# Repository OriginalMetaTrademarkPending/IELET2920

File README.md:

# IELET2920
Bachelor thesis on the research and development of next-generation handgrip trainers.

# Description of the task
In essence, the task is composed of the following parts:
- Mathematical modelling of the system. Due to the nature of this thesis, the model cannot be parameterized through a theoretical approach.
- Estimation of the parameters of the model. Referring to the point above, a least squares estimator has been used to estimate the model parameters.
- Kalman filter design. This is the final point of the design, which aims at improving the measurements, as well as estimating the hidden variable (fatigued muscle mass).

Here it is important to note that the task includes a significant amount of hardware design, especially in the domain of 3D-modelling, 3D-printing and PCB design.

# Parameter estimation

Until now, 5 tests have been completed. The results are shown below:

## Test 1: data.csv

$\theta_{af} = 0.0258$
$\theta_{ar} = 12.9653$
$\theta_{ra} = 1.8997$
$\theta_{fa} = 0.0230$
$M = 7.5095$
Sum of squares: 238.7625

## Test 2: test1.csv

$\theta_{af} = 0.0427$
$\theta_{ar} = 341.1526$
$\theta_{ra} = 3.1696$
$\theta_{fa} = 0.0747$
$M = 6.3241$
Sum of squares: 305.6513

## Test 3: test2.csv

$\theta_{af} = 0.0216$
$\theta_{ar} = 29.7083$
$\theta_{ra} = 4.9487$
$\theta_{fa} = 0$
$M = 7.4149$
Sum of squares: 297.8530

## Test 4: test3.csv

$\theta_{af} = 1.2019$
$\theta_{ar} = 75.4510$
$\theta_{ra} = 2.3210$
$\theta_{fa} = 1.0925$
$M = 12.1936$
Sum of squares: 954.0013

## Test 5: test4.csv

$\theta_{af} = 0.1093$
$\theta_{ar} = 517.0190$
$\theta_{ra} = 5.3904$
$\theta_{fa} = 0.1584$
$M = 5.9675$
Sum of squares: 767.8368

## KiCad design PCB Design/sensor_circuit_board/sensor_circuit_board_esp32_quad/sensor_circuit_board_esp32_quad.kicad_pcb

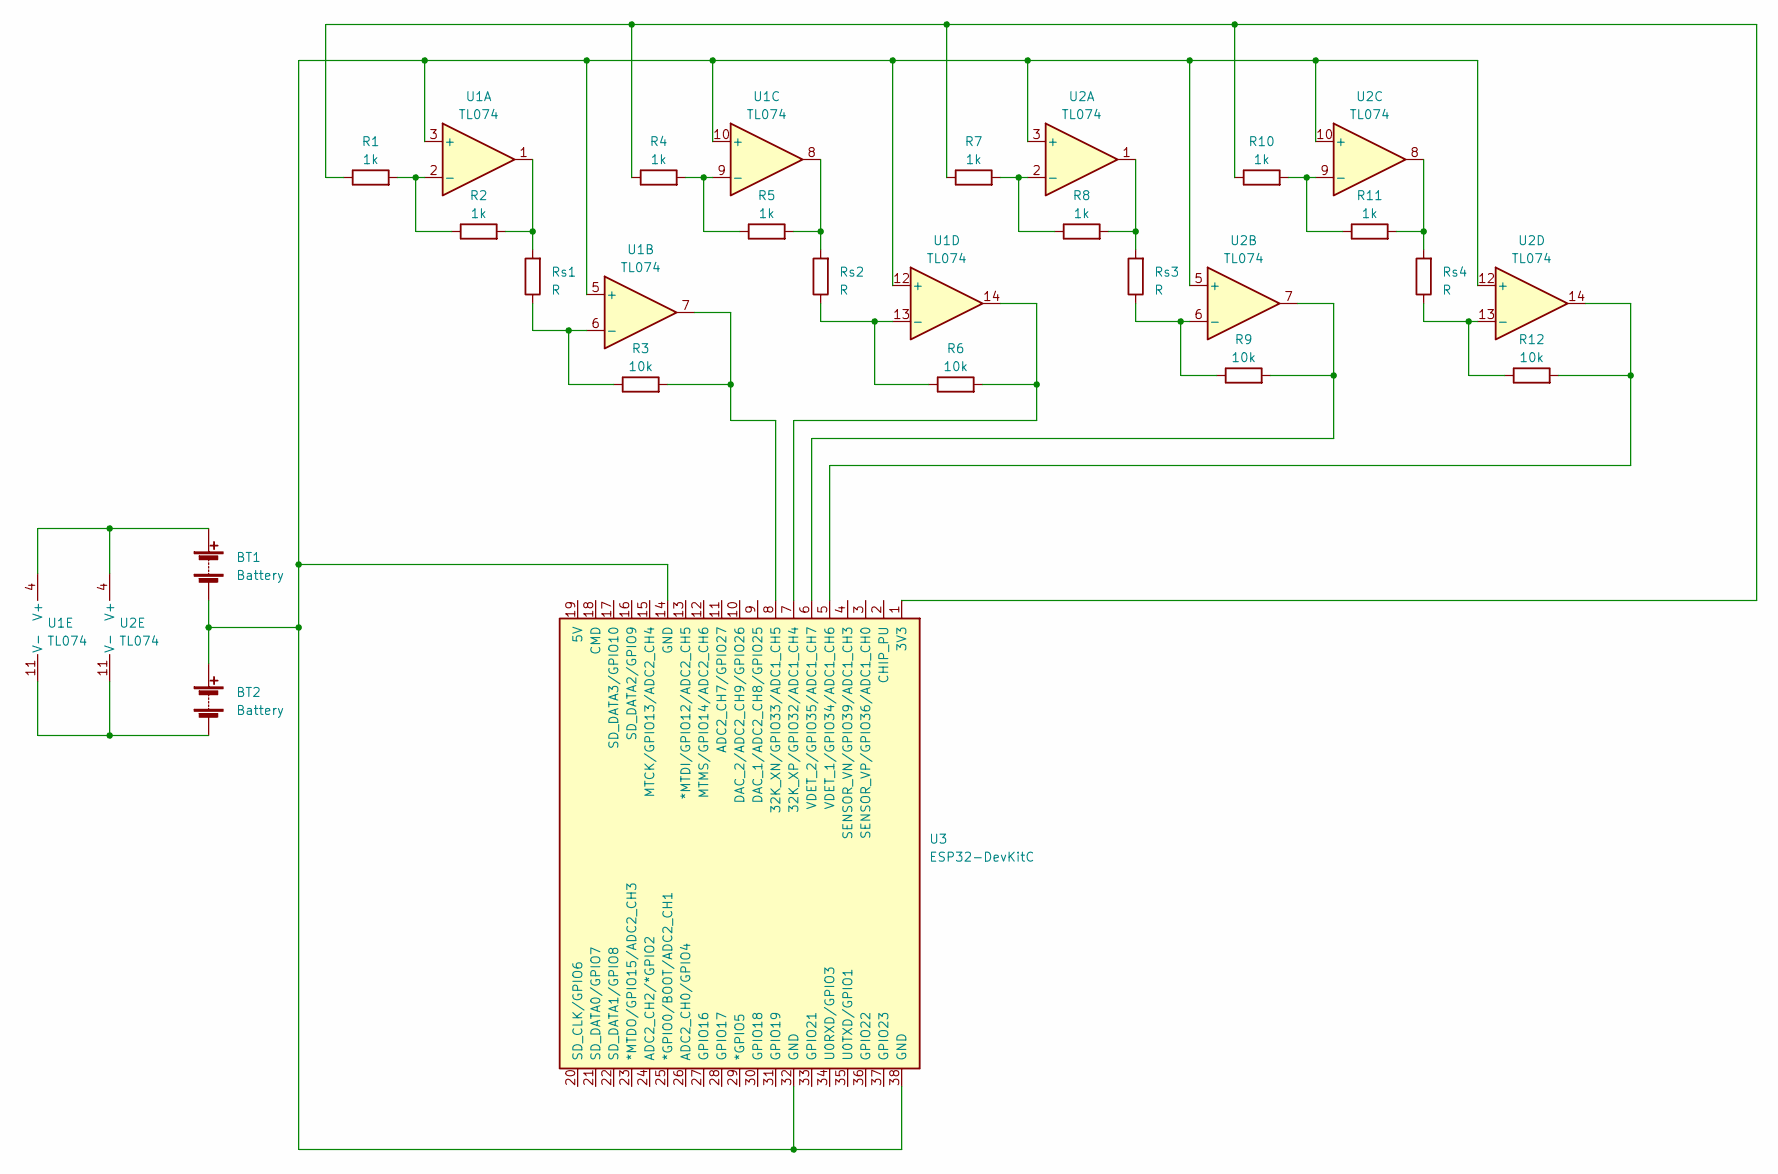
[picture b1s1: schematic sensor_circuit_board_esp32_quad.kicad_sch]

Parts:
BT1, BT2: Battery; BatteryHolder_Eagle_12BH611-GR
R1, R2, R4, R5, R7, R8, R10, R11: 1k; R_Axial_DIN0207_L6.3mm_D2.5mm_P7.62mm_Horizontal
R3, R6, R9, R12: 10k; R_Axial_DIN0207_L6.3mm_D2.5mm_P7.62mm_Horizontal
Rs1, Rs2, Rs3, Rs4: R; D_DO-15_P2.54mm_Vertical_AnodeUp
U1, U2: TL074; DIP-14_W7.62mm_LongPads
U3: ESP32-DevKitC

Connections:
unnamed: BT1.1 (+), U1.4 (V+), U2.4 (V+)
unnamed: BT1.2 (-), BT2.1 (+), U1.3 (+), U1.5 (+), U1.10 (+), U1.12 (+), U2.3 (+), U2.5 (+), U2.10 (+), U2.12 (+), U3.14 (GND), U3.32 (GND), U3.38 (GND)
unnamed: BT2.2 (-), U1.11 (V-), U2.11 (V-)
unnamed: R2.2, Rs1.2, U1.1
unnamed: R5.2, Rs2.2, U1.8
unnamed: R8.2, Rs3.2, U2.1
unnamed: R11.2, Rs4.2, U2.8
unnamed: R1.2, R2.1, U1.2 (-)
unnamed: R3.1, Rs1.1, U1.6 (-)
unnamed: R4.2, R5.1, U1.9 (-)
unnamed: R6.1, Rs2.1, U1.13 (-)
unnamed: R7.2, R8.1, U2.2 (-)
unnamed: R9.1, Rs3.1, U2.6 (-)
unnamed: R10.2, R11.1, U2.9 (-)
unnamed: R12.1, Rs4.1, U2.13 (-)
unnamed: R1.1, R4.1, R7.1, R10.1, U3.1 (3V3)
unnamed: R3.2, U1.7, U3.8 (32K_XN/GPIO33/ADC1_CH5)
unnamed: R6.2, U1.14, U3.7 (32K_XP/GPIO32/ADC1_CH4)
unnamed: R12.2, U2.14, U3.5 (VDET_1/GPIO34/ADC1_CH6)
unnamed: R9.2, U2.7, U3.6 (VDET_2/GPIO35/ADC1_CH7)

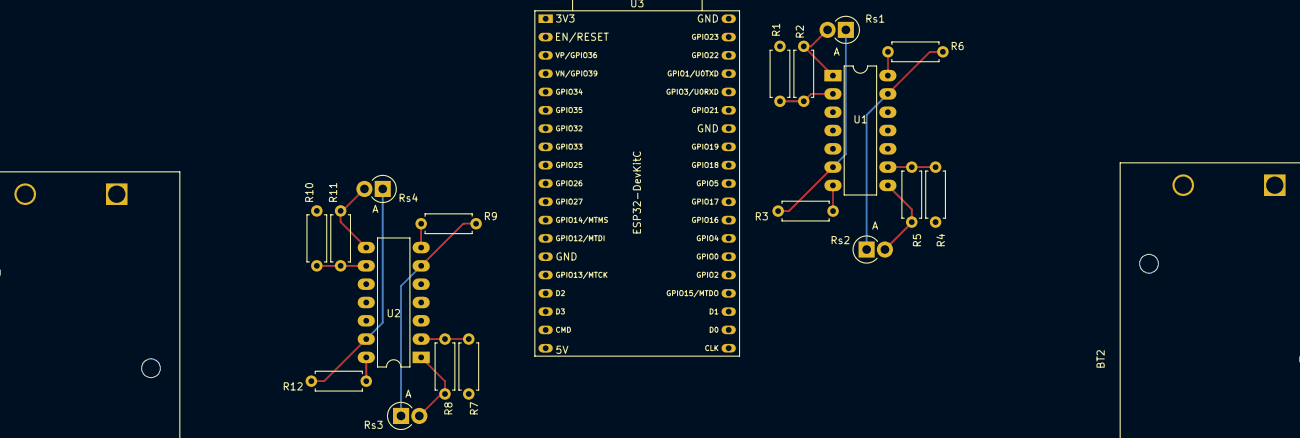
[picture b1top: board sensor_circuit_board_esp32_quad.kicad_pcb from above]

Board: 2 copper layers, 21 parts (0 on the bottom side), 20 nets.

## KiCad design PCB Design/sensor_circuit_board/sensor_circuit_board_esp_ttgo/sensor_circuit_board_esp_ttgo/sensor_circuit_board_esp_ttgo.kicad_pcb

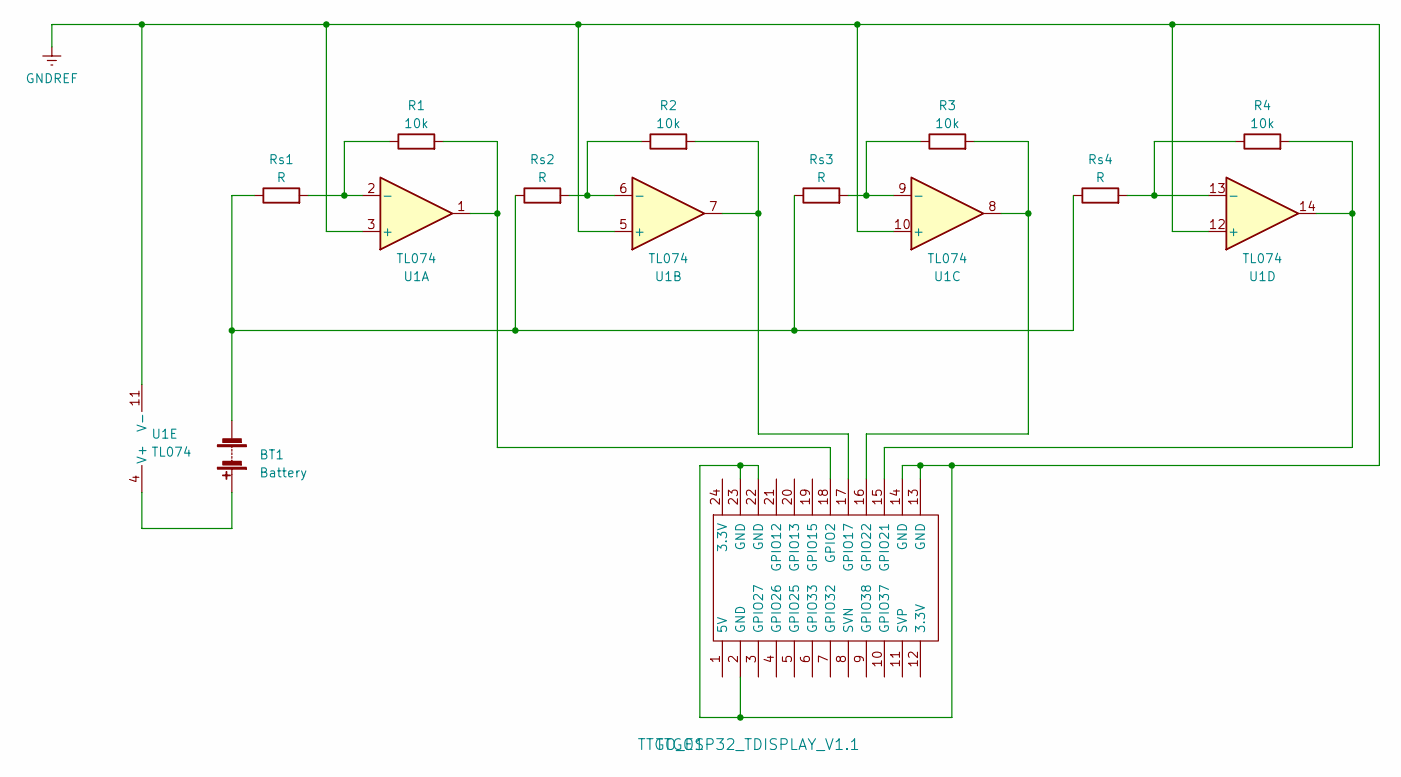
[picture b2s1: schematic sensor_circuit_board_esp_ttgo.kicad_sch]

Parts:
BT1: Battery; BatteryHolder_TruPower_BH-331P_3xAA
R1, R2, R3, R4: 10k; R_Axial_DIN0207_L6.3mm_D2.5mm_P7.62mm_Horizontal
Rs1, Rs2, Rs3, Rs4: R; D_DO-15_P2.54mm_Vertical_AnodeUp
TTGO1: TTGO_ESP32_TDISPLAY_V1.1; TTGO_ESP32_TDisplay_v1.1
U1: TL074; DIP-14_W7.62mm

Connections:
GNDREF: TTGO1.2 (GND), TTGO1.13 (GND), TTGO1.14 (GND), TTGO1.22 (GND), TTGO1.23 (GND), U1.3 (+), U1.5 (+), U1.10 (+), U1.11 (V-), U1.12 (+)
unnamed: BT1.1 (+), U1.4 (V+)
unnamed: BT1.2 (-), Rs1.1, Rs2.1, Rs3.1, Rs4.1
unnamed: R1.2, TTGO1.18 (GPIO2), U1.1
unnamed: R2.2, TTGO1.17 (GPIO17), U1.7
unnamed: R4.2, TTGO1.15 (GPIO21), U1.14
unnamed: R3.2, TTGO1.16 (GPIO22), U1.8
unnamed: R1.1, Rs1.2, U1.2 (-)
unnamed: R2.1, Rs2.2, U1.6 (-)
unnamed: R3.1, Rs3.2, U1.9 (-)
unnamed: R4.1, Rs4.2, U1.13 (-)

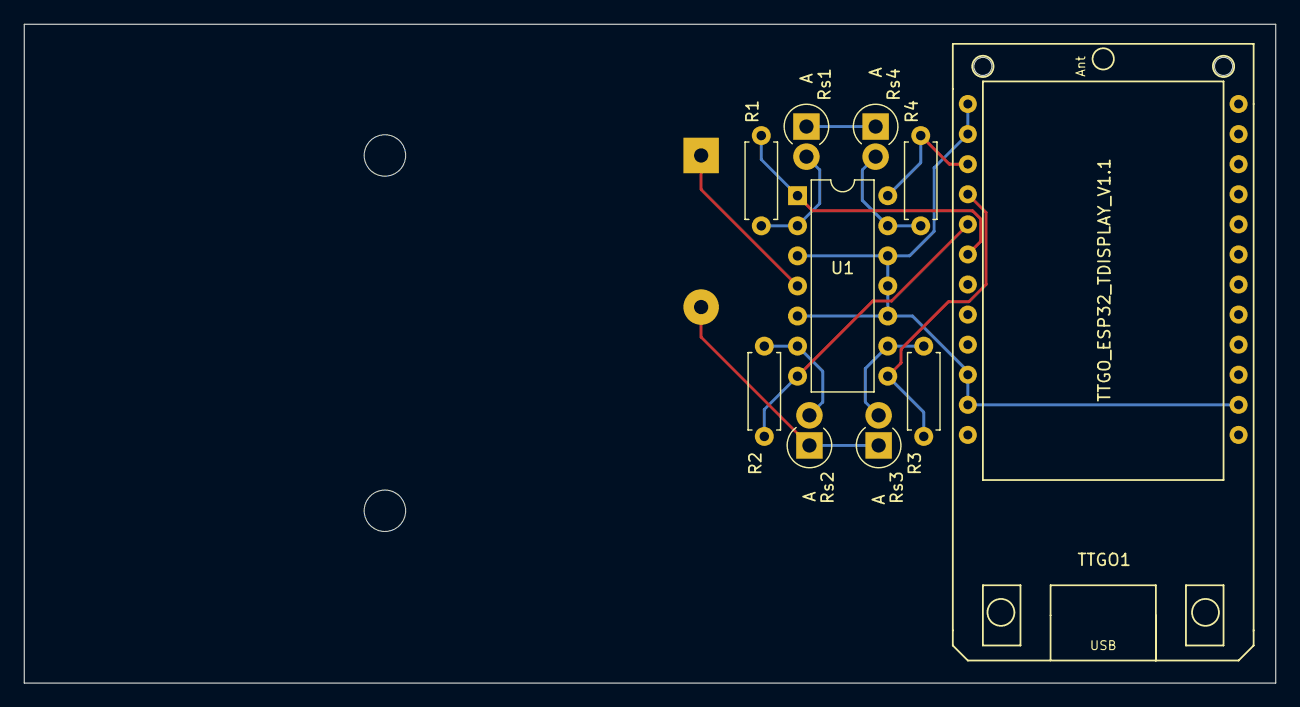
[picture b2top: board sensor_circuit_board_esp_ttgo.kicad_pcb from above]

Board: 2 copper layers, 105.7 x 55.6 mm, 11 parts (1 on the bottom side), 11 nets.

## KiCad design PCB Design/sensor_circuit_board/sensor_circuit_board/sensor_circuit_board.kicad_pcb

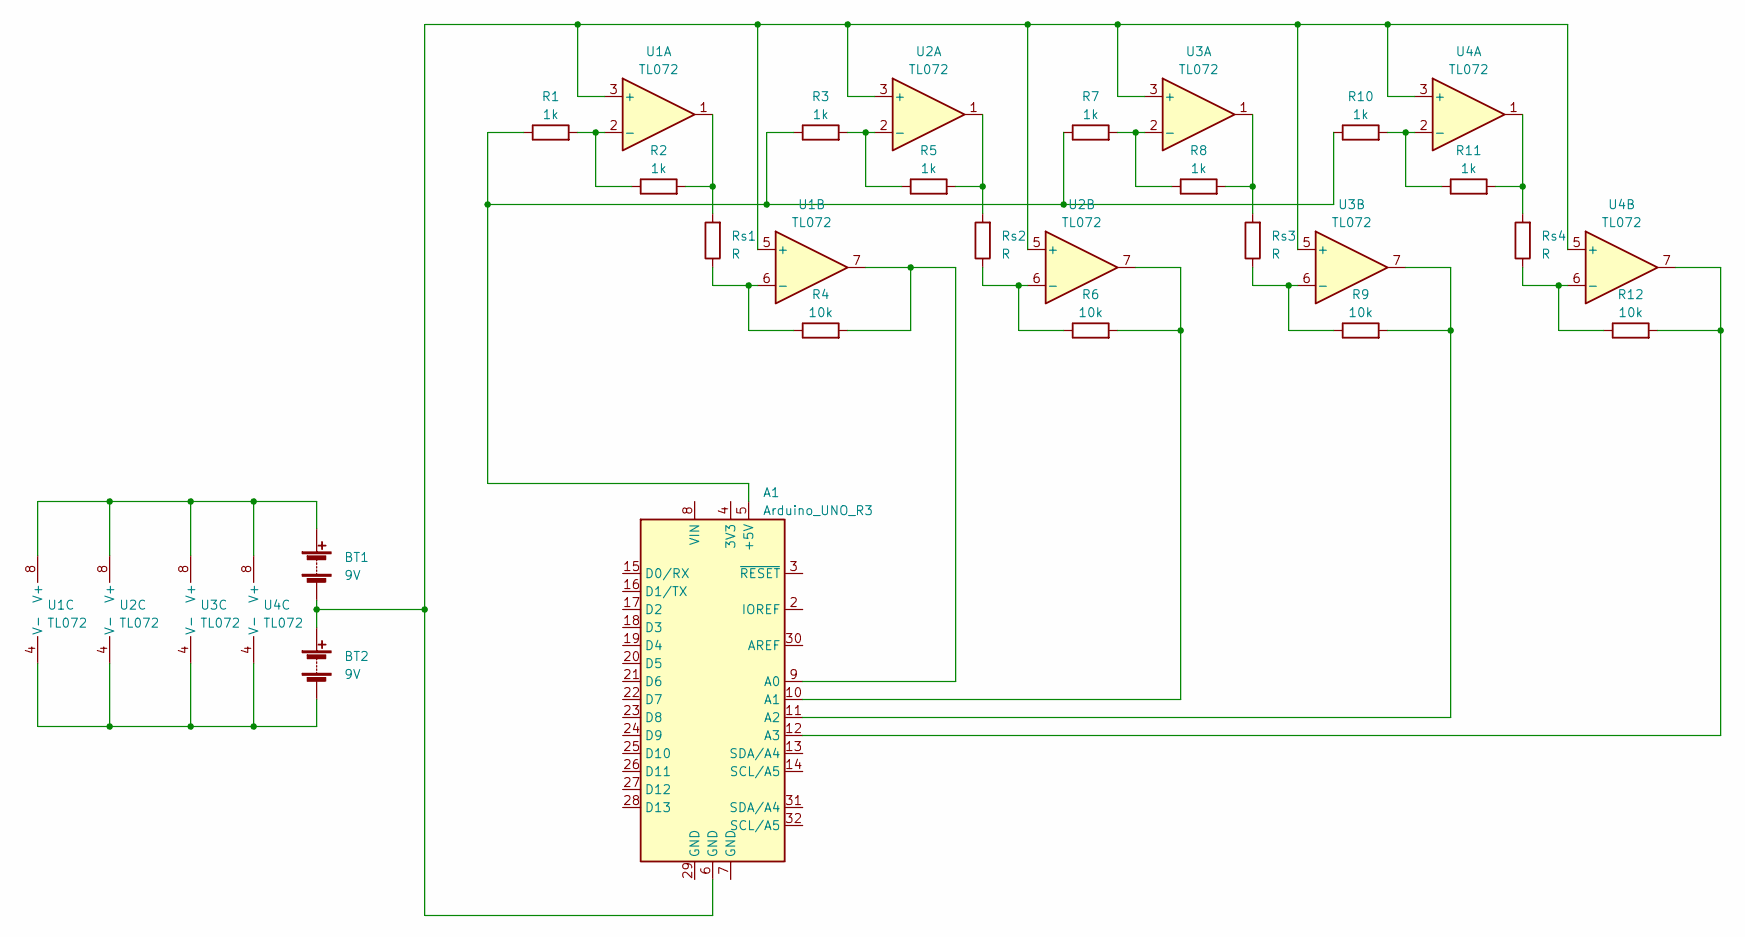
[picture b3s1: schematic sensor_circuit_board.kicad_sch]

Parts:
A1: Arduino_UNO_R3
BT1, BT2: 9V; BatteryHolder_Eagle_12BH611-GR
R1, R2, R3, R5, R7, R8, R10, R11: 1k; R_Axial_DIN0207_L6.3mm_D2.5mm_P7.62mm_Horizontal
R4, R6, R9, R12: 10k; R_Axial_DIN0207_L6.3mm_D2.5mm_P7.62mm_Horizontal
Rs1, Rs2, Rs3, Rs4: R; D_DO-15_P2.54mm_Vertical_AnodeUp
U1, U2, U3, U4: TL072; DIP-8_W7.62mm

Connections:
unnamed: A1.5 (+5V), R1.1, R3.1, R7.1, R10.1
unnamed: A1.9 (A0), R4.2, U1.7
unnamed: A1.10 (A1), R6.2, U2.7
unnamed: A1.11 (A2), R9.2, U3.7
unnamed: A1.12 (A3), R12.2, U4.7
unnamed: BT1.1 (+), U1.8 (V+), U2.8 (V+), U3.8 (V+), U4.8 (V+)
unnamed: A1.6 (GND), BT1.2 (-), BT2.1 (+), U1.3 (+), U1.5 (+), U2.3 (+), U2.5 (+), U3.3 (+), U3.5 (+), U4.3 (+), U4.5 (+)
unnamed: BT2.2 (-), U1.4 (V-), U2.4 (V-), U3.4 (V-), U4.4 (V-)
unnamed: R2.2, Rs1.2, U1.1
unnamed: R5.2, Rs2.2, U2.1
unnamed: R8.2, Rs3.2, U3.1
unnamed: R11.2, Rs4.2, U4.1
unnamed: R1.2, R2.1, U1.2 (-)
unnamed: R4.1, Rs1.1, U1.6 (-)
unnamed: R3.2, R5.1, U2.2 (-)
unnamed: R6.1, Rs2.1, U2.6 (-)
unnamed: R7.2, R8.1, U3.2 (-)
unnamed: R9.1, Rs3.1, U3.6 (-)
unnamed: R10.2, R11.1, U4.2 (-)
unnamed: R12.1, Rs4.1, U4.6 (-)

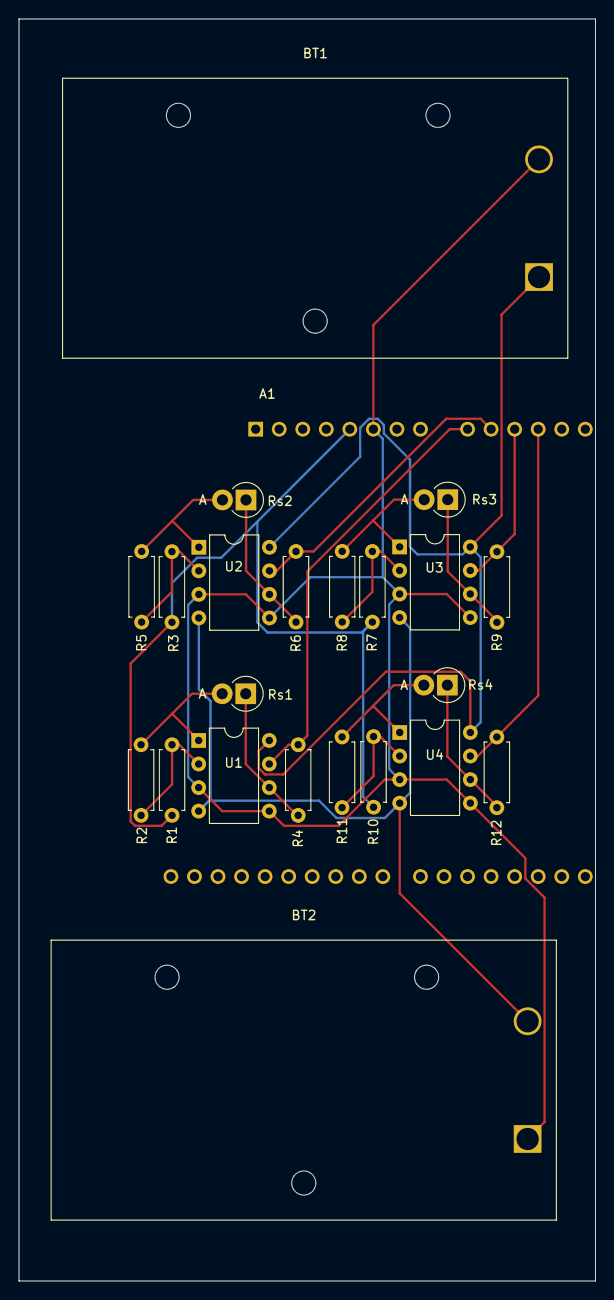
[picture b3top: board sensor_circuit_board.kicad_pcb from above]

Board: 2 copper layers, 62.2 x 136.1 mm, 23 parts (0 on the bottom side), 20 nets.

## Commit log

2023-03-22 Python scripts for least squares and data logging imported
2023-03-22 PCB design files
2023-03-22 ESP32 files for measurements
2023-03-22 Better organization of folders
2023-03-22 Better organization of folders v2
2023-03-22 Small changes to esp file. Fits the given circuit
2023-03-22 commented esp code
2023-03-22 Updated the README file
2023-03-23 Implemented basic kalman filter and basic graphing
2023-03-24 Added MATLAB code for system identification
2023-03-24 "Changed the theta-parameters
2023-03-26 "Added a few guesstimates for the theta-parameters, as well as a few practical rules to help the intuition regarding the model"
2023-03-26 Added a .csv data extractor for the least squares estimator.
2023-03-28 System identification and new PCB
2023-03-28 Deleted PCB folder due to naming errors for Ole
2023-03-28 added all sensors
2023-03-29 added new scale
2023-03-29 Fixed least squares estimator and the measurement files. The first part of the pipeline is now complete.
2023-03-30 removed the unneeded and added customization
2023-03-31 Measured some more stuff, minor changes, got a good least squares run
2023-04-03 Changes in MATLAB scripts - continous time script needs to be changed (set as todo in next commit)
2023-04-03 Changed the scripts so that deval is not used. Instead, we append the final results of the 4th (5th) order Runge-Kutta method to the solutions vector, which is then used to solve the optimization pro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
2023-04-05 Changes to parameter estimation
2023-04-05 Performed 4 tests for parameter estimation
2023-04-05 Plotted the test results from today, saved them as jpgs
2023-04-05 Plotted the test results as jpgs
2023-04-06 Reorganized the MATLAB folder
2023-04-08 Bring out your testsgit add *! Bring out your testsgit add *
2023-04-09 Wrote the code for the 3-state model, bringing out tests tomorrow
2023-04-09 A little bit of filesystem cleanup. Code for parameter estimation for the 3-state model is also done, will run the necessary simulations tomorrow
2023-04-10 Started sensor integrations, calibrated 2 sensors
2023-04-10 Filesystem cleanup
2023-04-10 Completed some of the 2-sensor tests. Test 4 is not correct due to signal noise (don't know why that happened,will check tomorrow)
2023-04-11 changes to the MATLAB scripts. Moving average filter didn't work as expected in MATLAB, will try to implement it in the measurement circuit
2023-04-12 Changes in sample time, moving average filter, time horizon for the model, and many more things. The trends we want aren't visible yet...will check the hardware for noise sources.
2023-04-13 Tuning MA filter, trying to eliminate noise.
2023-04-13 test commit
2023-04-13 Committing
2023-04-13 test file & esp python
2023-04-13 test1 done
2023-04-13 test2
2023-04-13 test3
2023-04-13 more tests
2023-04-13 changes to MATLAB code for the new tests
2023-04-13 test 3 10ms
2023-04-13 New changes
2023-04-13 removed test files due to noise. Will be making the tests at a new branch called parameter_estimation
2023-04-13 Opened a new branch for parameter estimation. Purpose of this branch is to fix the estimation algorithm
2023-04-14 added .pio
2023-04-14 Massive changes to code, and perhaps a new success???
2023-04-14 good parameters
2023-04-14 4 new tests
2023-04-17 Circuit and PCB
2023-04-17 estimate of sensor meassurment
2023-04-17 Implemented the first part of the estimator (Kalman Filter). Trying to find a solution for the least squares estimator
2023-04-17 Changes in the new estimator, will try to finalize tomorrow
2023-04-19 Full Kalman Filter implementation in MATLAB
2023-04-19 estimate R changes
2023-04-19 M - changes
2023-04-19 added matrix multiplication library
2023-04-19 matrix multiplication with examples
2023-04-19 New parameter estimation changes
2023-04-19 testing moving avarage
2023-04-19 tests with moving avarage filter
2023-04-19 git playing games
2023-04-19 tests
2023-04-19 New changes to parameter estimation
2023-04-20 bigger movavg
2023-04-20 functions for arduino code
2023-04-20 updating
2023-04-20 functions for arduino
2023-04-20 new esp testdocument
2023-04-20 added all libraries
2023-04-20 removed clutter from code
2023-04-21 3 dimensional filter
2023-04-23 added phi, not tested
2023-04-24 Last changes to the files
2023-04-24 non working states
2023-04-24 working Kalman filter
2023-04-24 cleaned up
2023-04-24 cleanup
2023-04-24 initialized top and topmid sensor
2023-04-25 missing fatigue, imput signal must be defined
2023-04-25 working model change
2023-04-26 all sensors in use
2023-04-26 all sensors test
2023-04-26 Updates in fit code
2023-04-26 test bias1 and 2
2023-04-26 working display for all sensors
2023-04-28 prettier code
2023-04-28 agin better code
2023-04-28 Changes in parameter estimation code
2023-04-28 JSON file update
2023-05-01 refreshing
2023-05-01 more testbias
2023-05-03 Plots for the report, as well as a new constraint calculation
2023-05-08 cleanup git
2023-05-08 more cleanup
2023-05-08 Last changes in the master branch
2023-05-08 Deleting uneccesary files from the branch
2023-05-08 File deletion to fix the merge conflict into master
2023-05-12 Final updates to the code
2023-05-17 Last commit?
2023-05-17 Changes to gitignore
2023-05-17 Fixing rebase(hopefully)?
2023-05-17 Fixing rebase(hopefully?)
2023-05-19 Changed the legend
2023-05-19 Renamed movavg tests
2023-05-19 Changes in bias test 3
2023-05-20 prettier ESP code
2023-05-20 added 3d model files
2023-05-20 structural changes in files
2023-05-20 removed showcase files
2023-05-23 kicad update
2023-05-29 Better derivative, works alot better
2023-05-31 better estimation of u. Still needs a proper estimate
2023-06-03 Solving the merge conflicts
2024-07-30 Fixed some corrupted EDA files which went unchecked during the project hand-in. They can now be opened. Persistent bug regarding SPICE simulation of schematic cannot be solved, will check for possibl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
2024-07-30 Found SPICE models for simulation of the circuit with TL074 opamps. Will check if we can find simulation models for TL071 opamps.
2025-06-22 Removed the asv files, added electronics backups and standardized the naming of the datasets.
2025-06-28 Changes to the grid search and removed the KF methods.
2025-08-22 Reverted the bachelor_esp_kalman file to functioning (?) version.
2025-08-22 Removed the striped lines in MATLAB parameter estimation plot code.
